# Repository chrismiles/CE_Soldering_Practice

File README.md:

CE_Soldering_Practice
=====================

A board for learning how to solder without breaking anything.

Includes:

* Custom footprints:

  * Zener Diode Array IC (BZX84C5V1S-7-F) http://www.digikey.com.au/product-detail/en/BZX84C5V1S-7-F/BZX84C5V1S-FDICT-ND/717871
  * Pushbutton Switch (KS-01Q-01) http://www.digikey.com.au/product-detail/en/KS-01Q-01/EG4791-ND/2116270
  * MOSFET (IRF7607TRPBF) http://www.digikey.com.au/product-detail/en/IRF7607TRPBF/IRF7607TRPBFCT-ND/2441014
  * LM324 OPAMP (LM324DR) http://www.digikey.com.au/product-detail/en/LM324DR/296-14597-1-ND/555529
  * Voltage Regulator IC (TPS54325PWPR) http://www.digikey.com.au/product-detail/en/TPS54325PWPR/296-24557-1-ND/2074508

* Traces and VIAs.
* Custom silk screen (soldering iron graphic)
* Surface mount passive components: 1206, 0603, 0805 resistors and capacitors
* MSOP: MOSFET (IRF7607TRPBF)
* TSSOP: Zener Diode Array IC (BZX84C5V1S-7-F)
* SOIC: LM324 OPAMP (LM324DR)
* Through hole: Pushbutton Switch (KS-01Q-01); BJT transistors
* A part with a large power pad: Voltage Regulator IC (TPS54325PWPR)

PCB 3D:

PCB:

Gerber:

Schematic:

Netlist:

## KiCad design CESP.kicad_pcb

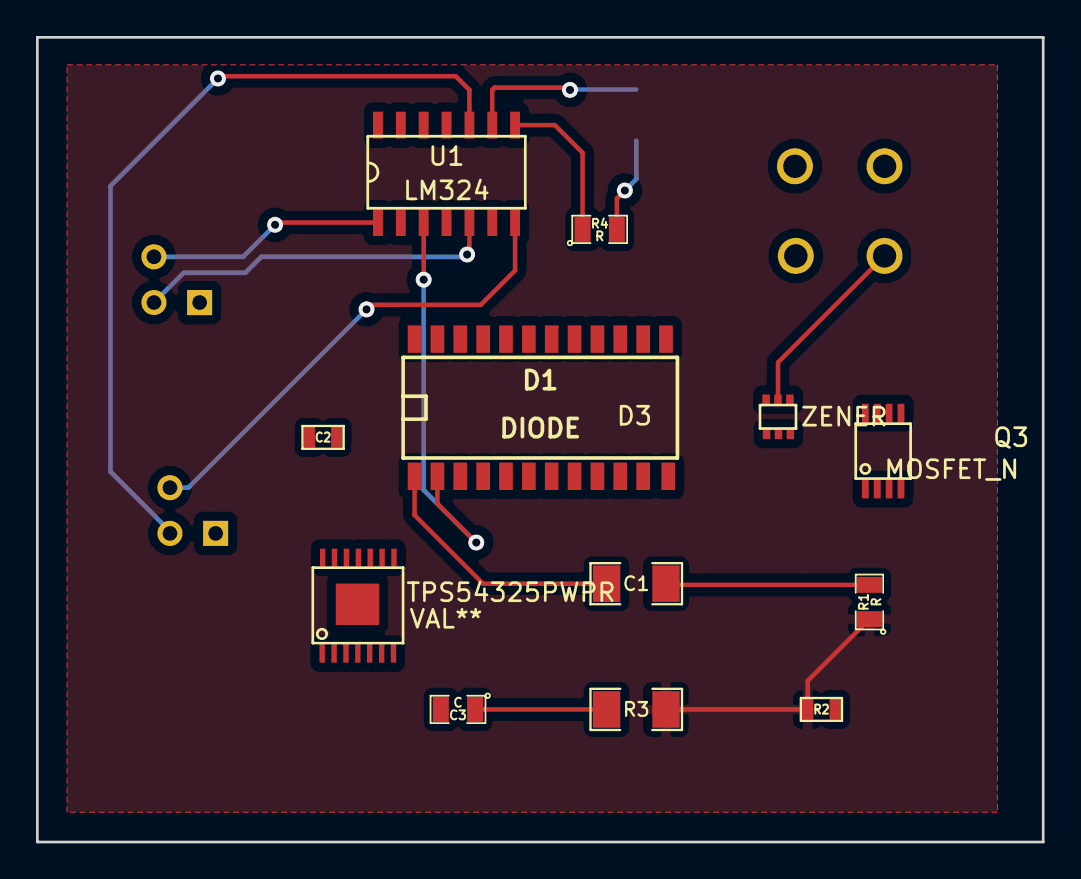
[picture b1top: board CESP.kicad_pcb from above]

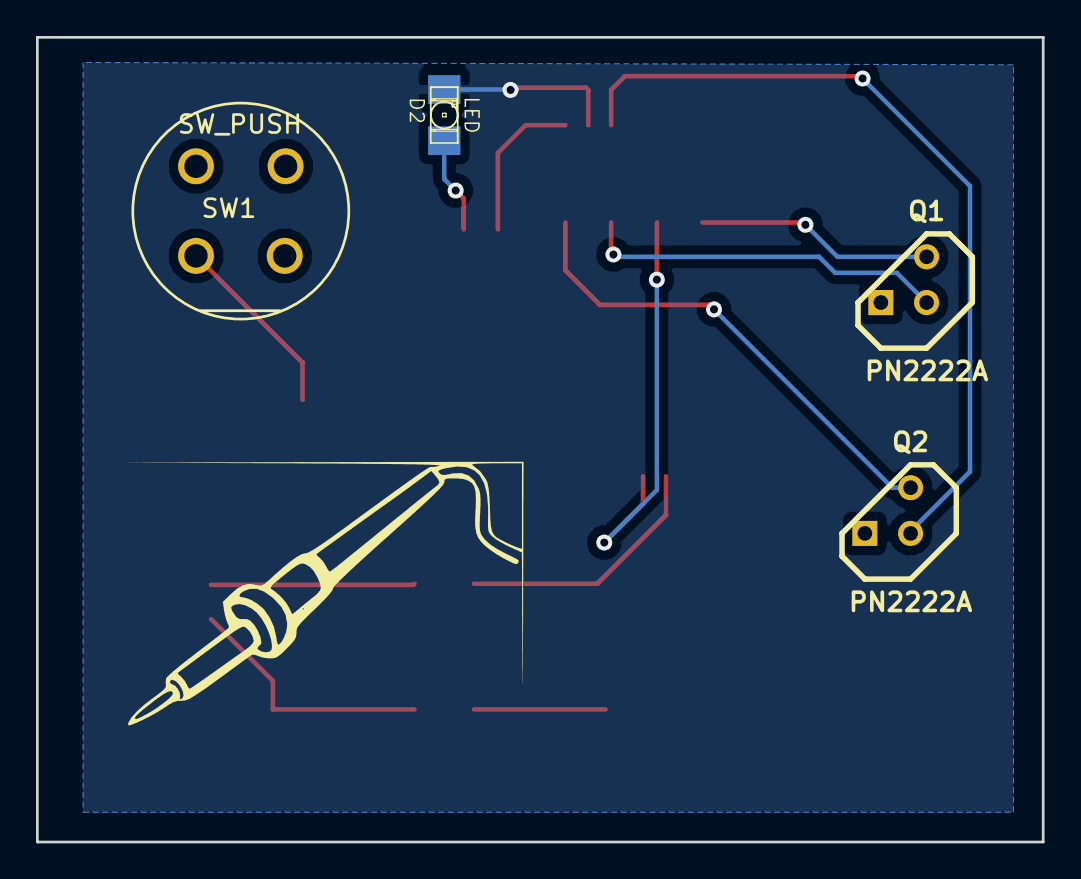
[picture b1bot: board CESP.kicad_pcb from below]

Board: 2 copper layers, 55.9 x 44.7 mm, 16 parts (4 on the bottom side), 13 nets.

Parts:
C1: C; SM1206
C2: C; SM0603
C3: C; SM0805
D1: DIODE; SOIC24
D2: LED; LED-1206
D3: ZENER; BZX84C5V1S-7-F
Q1, Q2: PN2222A; TO92
Q3: MOSFET_N; IRF7607TRPBF
R1, R4: R; SM0805
R2: R; SM0603
R3: R; SM1206
SW1: SW_PUSH; EG4791-ND
TPS54325PWPR: VAL**; TPS54325PWPR
U1: LM324; LM324DR

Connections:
GND: D2.2, U1.6, U1.9
unnamed: Q2.2, U1.10
unnamed: Q2.3, U1.7
unnamed: C1.1, R1.2
unnamed: C3.1, R3.2
unnamed: C1.2, D1.1
unnamed: D3.2, SW1.1
unnamed: D2.1, R4.2
unnamed: R4.1, U1.8
unnamed: Q1.2, U1.5
unnamed: D1.2, U1.3
unnamed: Q1.3, U1.1
VCC: R1.1, R2.1, R3.1

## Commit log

2014-01-28 Laid out a PCB with all required component types.
